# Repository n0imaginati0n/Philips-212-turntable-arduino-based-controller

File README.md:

# Philips-212-turntable-arduino-based-controller

A controller upgrade for the classic Philips 212 Hi-Fi turntable.
Replaces all touch switch, motor control, and auto-off functions with an Arduino Uno clone

Files include Arduino sketch and KiCad files

Fork of the

[lens42 project](https://github.com/lens42/Philips-212-turntable-arduino-based-controller)

[Details:](https://lensprojects.wordpress.com/2019/01/08/philips-212-turntable-controller-upgrade/)

# Improvements

* Use of the Ardino Pro Mini
* Self-made PCB. There are not so many parts there, it can be etched at home
* review schematics
    - add necessay loading on the LM780x. According to the datasheet, minimal current is 5..10 mA.
    - LM780x don't like to work on big capacitance load - they need protection diodes
    - small filtering caps on the sensors input to filter noise. input cirquit can be taken from original GA212 schematics
    - resistance in the MOSFET gate cirquit to limit the pulse current through MCU output
    - allow TH componets usage, reuse some items from original board
    - IP pins can be assigned better to make less croddings on the PCB
    - sensor button connections can be done better. but analog curcit rules should be taken into account
    - as I plan to etch teh single-layer board at home, I will use tow heatsinks for LM780x instead of the PCB polygons. There 
        is a lot of space under the PCB.
* Programming UART pins and reset button on the board. Pro Mini hasn't USB socket.
* Review the firmware
    - make it interactive
    - all initially predefined values can be set by UART
    - keep configuration values in the FLASH

# Arduino Power

Almost all Arduino boards has an LDO onboard. This LDO allows up to 16V input and can supply arduino and external cirquit 
with the +3.3V/+5V <150mA power according to the Arduino version. All the MCU ATMEGA328 allow both +3.3V and +5V power. The 
difference is that on lower voltage Arduino works stable with less crystal frequency. That is why +3.3V has 8MHz crystal and 
+5V has 16MHz crystal. Any version of the Arduino Pro Mini can safely be supplied with the +5V.

LM393 can operate with power in +2V..+36V range, means it can be perfectly powered from any version of the Arduino. It 
cosumes <20mA, this current is a maximal sink current and should be lower than that.

Unfortunately, my Arduino LDO is broken because of the previous experiments, that is why I kept the external LDO here and lead 
the +5V to the Arduino Vcc input. Vcc - is a direct way to teh Arduino power excluding on-baord LDO.

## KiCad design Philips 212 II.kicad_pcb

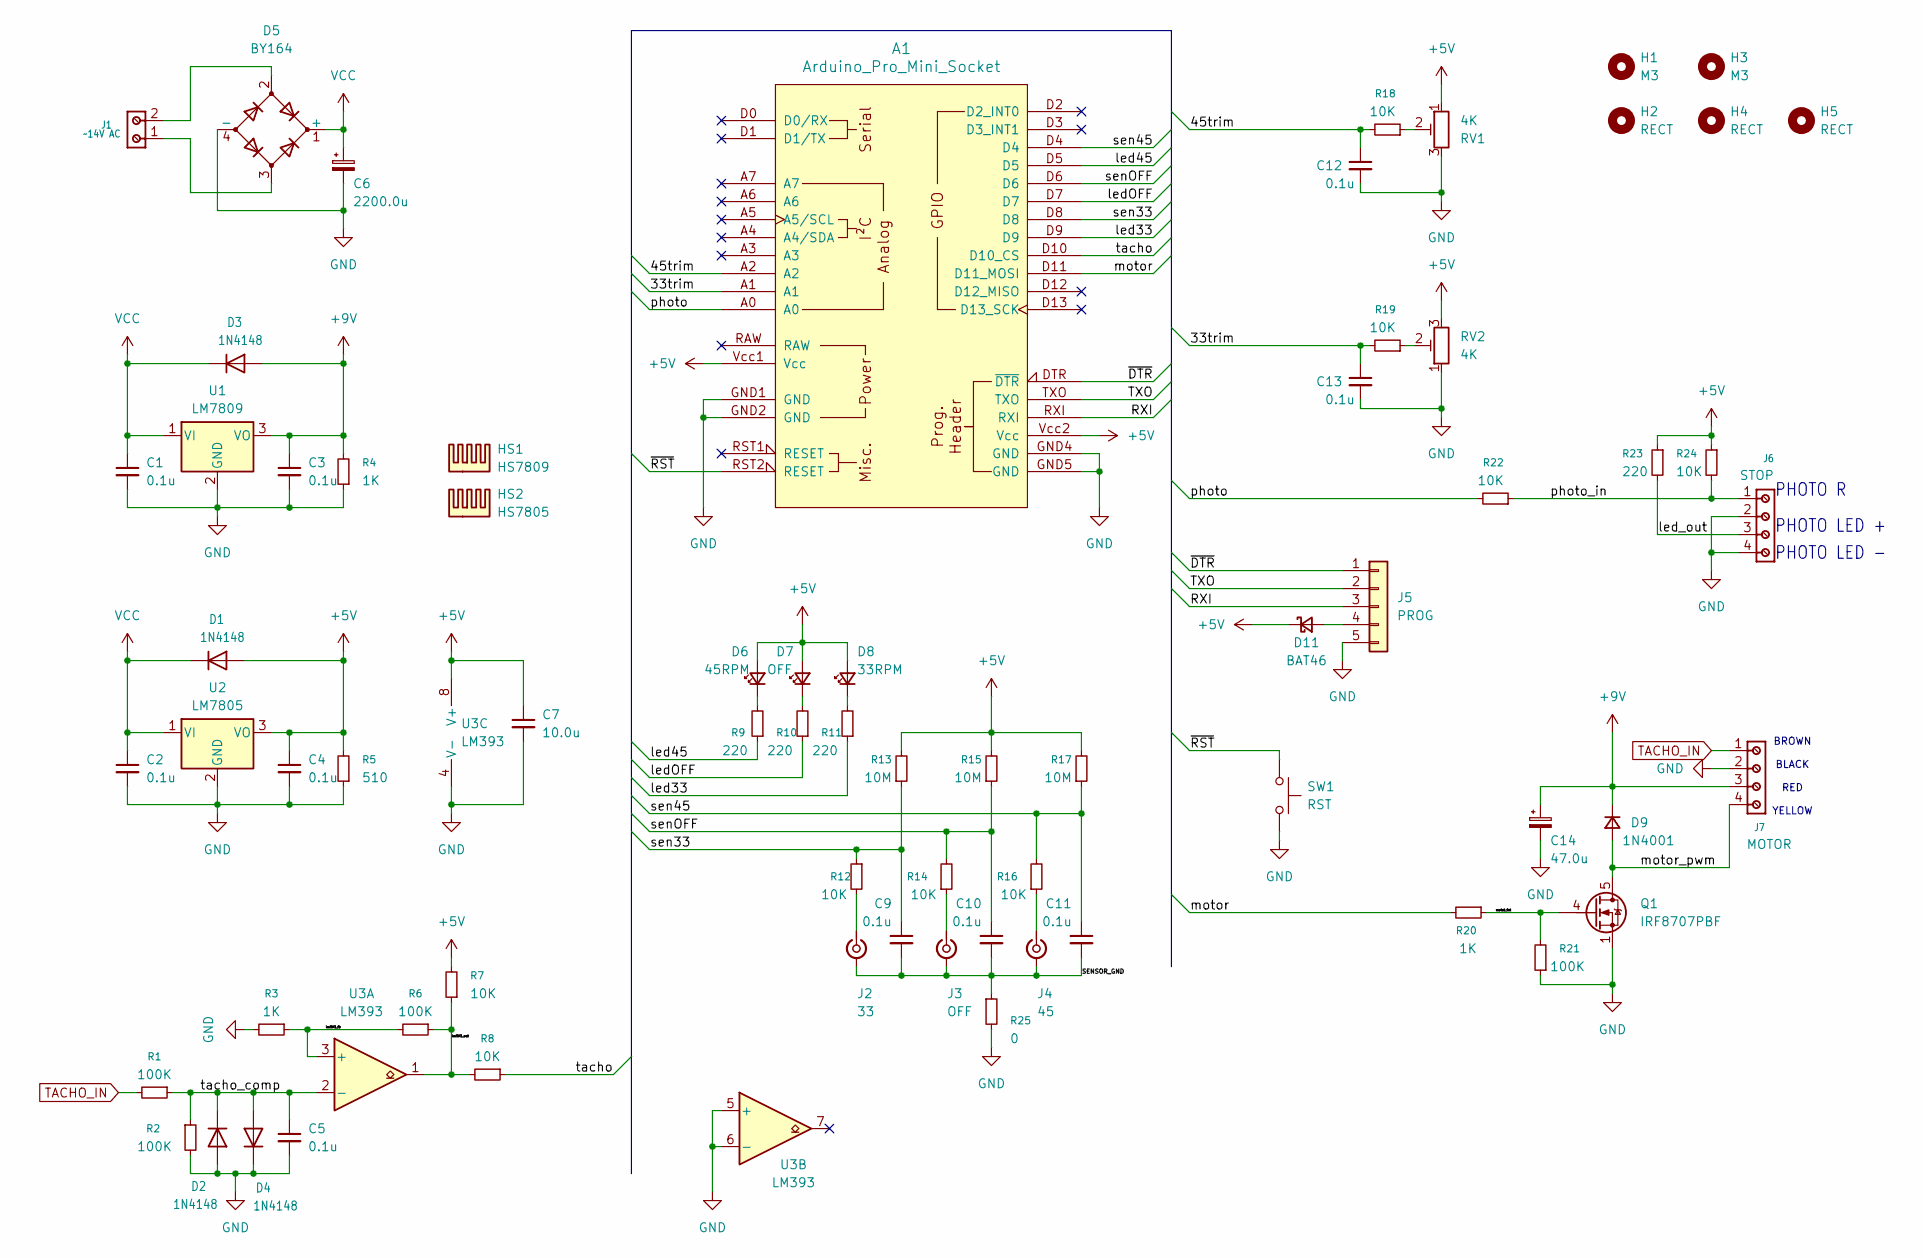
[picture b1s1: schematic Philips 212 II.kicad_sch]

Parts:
A1: Arduino_Pro_Mini_Socket
C1, C2, C3, C4, C5, C9, C10, C11, C12, C13: 0.1u; C_0805_2012Metric_Pad1.18x1.45mm_HandSolder
C6: 2200.0u; CP_Radial_D16.0mm_P7.50mm
C7: 10.0u; CP_Radial_D8.0mm_P3.50mm
C14: 47.0u; CP_Radial_D8.0mm_P3.50mm
D1, D3: 1N4148; D_MELF_Handsoldering
D2, D4: 1N4148; D_DO-35_SOD27_P7.62mm_Horizontal
D5: BY164; Diode_Bridge_19.0x3.5x10.0mm_P5.0mm
D6: 45RPM; LED_D5.0mm_Horizontal_O6.35mm_Z15.0mm
D7: OFF; LED_D5.0mm_Horizontal_O6.35mm_Z15.0mm
D8: 33RPM; LED_D5.0mm_Horizontal_O6.35mm_Z15.0mm
D9: 1N4001; D_DO-41_SOD81_P10.16mm_Horizontal
D11: BAT46; D_DO-35_SOD27_P7.62mm_Horizontal
H1, H3: M3; MountingHole_3.2mm_M3
H2, H4, H5: RECT; MountingHole_6mm
HS1: HS7809; FISHER-FK211-32_TO220_Horizontal
HS2: HS7805; FISHER-FK211-32_TO220_Horizontal
J1: ~14V AC; Altech_AK100_1x02_P5.00mm
J2: 33; Altech_AK100_1x02_P5.00mm
J3: OFF; Altech_AK100_1x02_P5.00mm
J4: 45; Altech_AK100_1x02_P5.00mm
J5: PROG; PinHeader_1x05_P2.54mm_Vertical
J6: STOP; Altech_AK100_1x04_P5.00mm
J7: MOTOR; Altech_AK100_1x04_P5.00mm
Q1: IRF8707PBF; PowerPAK_SO-8_Single
R1, R2, R21: 100K; R_0805_2012Metric_Pad1.20x1.40mm_HandSolder
R3: 1K; R_0805_2012Metric_Pad1.20x1.40mm_HandSolder
R4, R20: 1K; R_Axial_DIN0207_L6.3mm_D2.5mm_P7.62mm_Horizontal
R5: 510; R_Axial_DIN0207_L6.3mm_D2.5mm_P7.62mm_Horizontal
R6: 100K; R_Axial_DIN0207_L6.3mm_D2.5mm_P7.62mm_Horizontal
R7, R12, R14, R16, R18, R19, R22, R24: 10K; R_0805_2012Metric_Pad1.20x1.40mm_HandSolder
R8: 10K; R_Axial_DIN0207_L6.3mm_D2.5mm_P7.62mm_Horizontal
R9, R10, R11, R23: 220; R_Axial_DIN0207_L6.3mm_D2.5mm_P7.62mm_Horizontal
R13, R15, R17: 10M; R_Axial_DIN0411_L9.9mm_D3.6mm_P15.24mm_Horizontal
R25: 0; R_0805_2012Metric_Pad1.20x1.40mm_HandSolder
RV1, RV2: 4K; Potentiometer_ACP_CA14V-15_Vertical_Hole
SW1: RST; SW_PUSH_6mm
U1: LM7809; TO-220-3_Horizontal_TabDown
U2: LM7805; TO-220-3_Horizontal_TabDown
U3: LM393; SOIC-8_3.9x4.9mm_P1.27mm

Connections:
+5V: A1.Vcc1 (Vcc), A1.Vcc2 (Vcc), C4.1, C7.1, D1.2 (A), D6.2 (A), D7.2 (A), D8.2 (A), D11.1 (K), R5.2, R7.2, R13.2, R15.2, R17.2, R23.1, R24.1, RV1.1, RV2.3, U2.3 (VO), U3.8 (V+)
+9V: C3.1, C14.1, D3.2 (A), D9.1 (K), J7.3, R4.2, U1.3 (VO)
/33trim: A1.A1, C13.1, R19.2
/45trim: A1.A2, C12.1, R18.2
/RXI: A1.RXI, J5.3
/SENSOR_GND: C9.2, C10.2, C11.2, J2.2 (Ext), J3.2 (Ext), J4.2 (Ext), R25.1
/TXO: A1.TXO, J5.2
/led33: A1.D9, R11.1
/led45: A1.D5, R9.1
/ledOFF: A1.D7, R10.1
/led_out: J6.3, R23.2
/lm393_fb: R3.1, R6.2, U3.3 (+)
/lm393_out: R6.1, R7.1, R8.2, U3.1
/motor: A1.D11 (D11_MOSI), R20.2
/motor_pwm: D9.2 (A), J7.4, Q1.5 (D)
/motot_fet: Q1.4 (G), R20.1, R21.2
/photo: A1.A0, R22.2
/photo_in: J6.1, R22.1, R24.2
/sen33: A1.D8, C9.1, R12.1, R13.1
/sen45: A1.D4, C11.1, R16.2, R17.1
/senOFF: A1.D6, C10.1, R14.2, R15.1
/tacho: A1.D10 (D10_CS), R8.1
/tacho_comp: C5.1, D2.1 (K), D4.2 (A), R1.1, R2.1, U3.2 (-)
/~DTR: A1.DTR (~DTR), J5.1
/~RST: A1.RST2 (RESET), SW1.1
GND: A1.GND1 (GND), A1.GND2 (GND), A1.GND4 (GND), A1.GND5 (GND), C1.2, C2.2, C3.2, C4.2, C5.2, C6.2, C7.2, C12.2, C13.2, C14.2, D2.2 (A), D4.1 (K), D5.4 (-), J5.5, J6.2, J6.4, J7.2, Q1.1 (S), Q1.2 (S), Q1.3 (S), R2.2, R3.2, R4.1, R5.1, R21.1, R25.2, RV1.3, RV2.1, SW1.2, U1.2 (GND), U2.2 (GND), U3.4 (V-), U3.5 (+), U3.6 (-)
unnamed: D5.2, J1.2
unnamed: D5.3, J1.1
unnamed: D6.1 (K), R9.2
unnamed: D7.1 (K), R10.2
unnamed: D8.1 (K), R11.2
unnamed: D11.2 (A), J5.4
unnamed: J2.1 (In), R12.2
unnamed: J3.1 (In), R14.1
unnamed: J4.1 (In), R16.1
unnamed: R18.1, RV1.2
unnamed: R19.1, RV2.2
TACHO_IN: J7.1, R1.2
VCC: C1.1, C2.1, C6.1, D1.1 (K), D3.1 (K), D5.1 (+), U1.1 (VI), U2.1 (VI)

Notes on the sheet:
PHOTO R
PHOTO LED -
BROWN BLACK RED YELLOW
PHOTO LED +

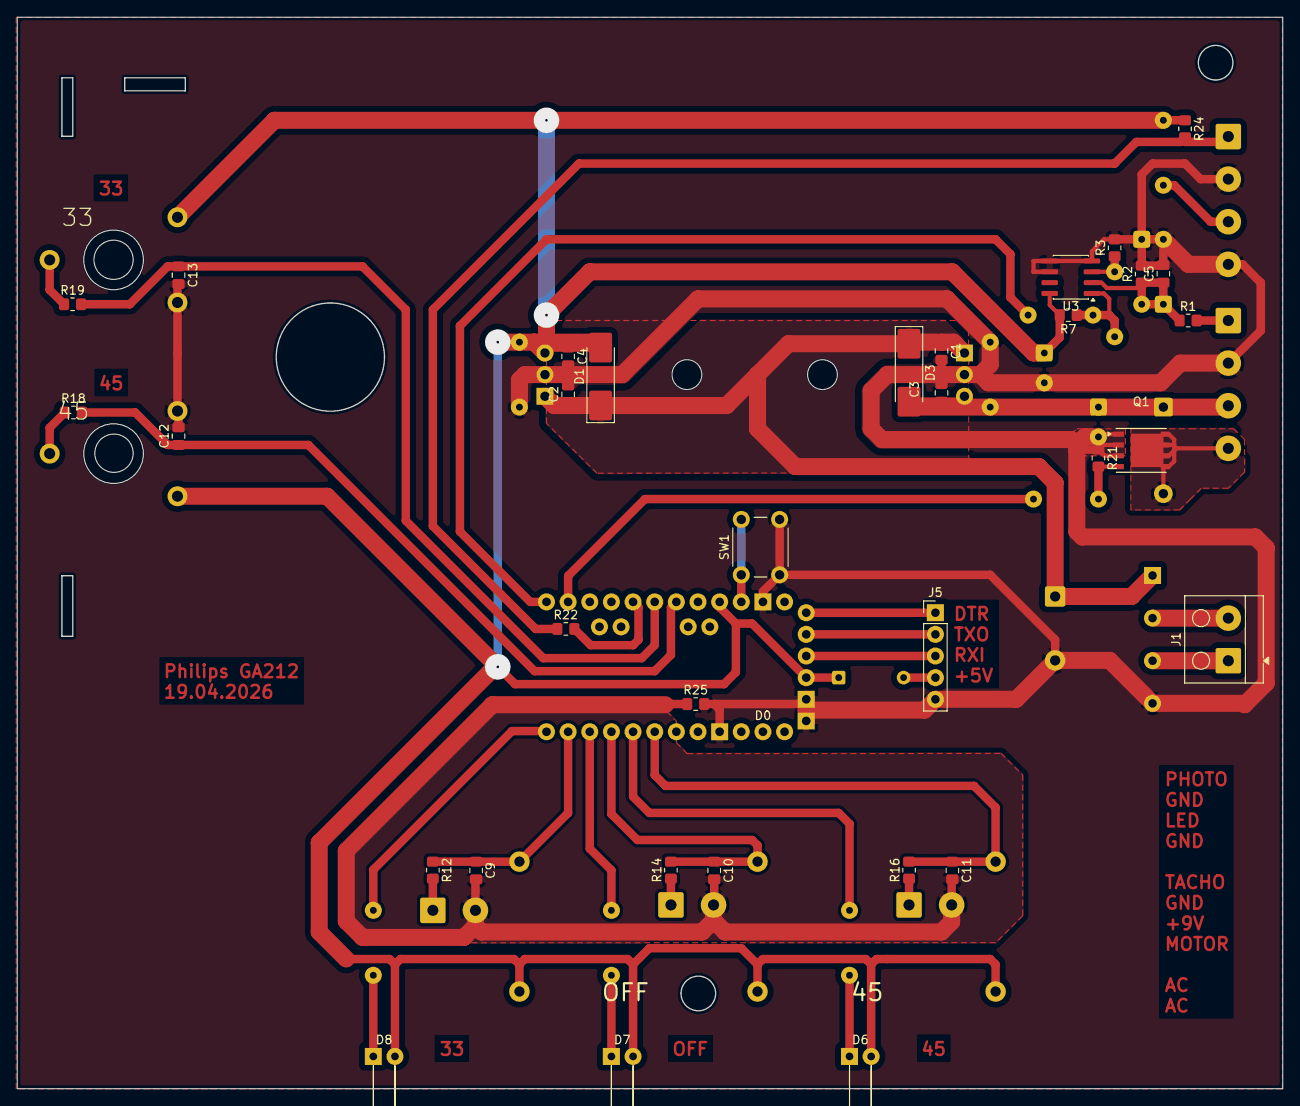
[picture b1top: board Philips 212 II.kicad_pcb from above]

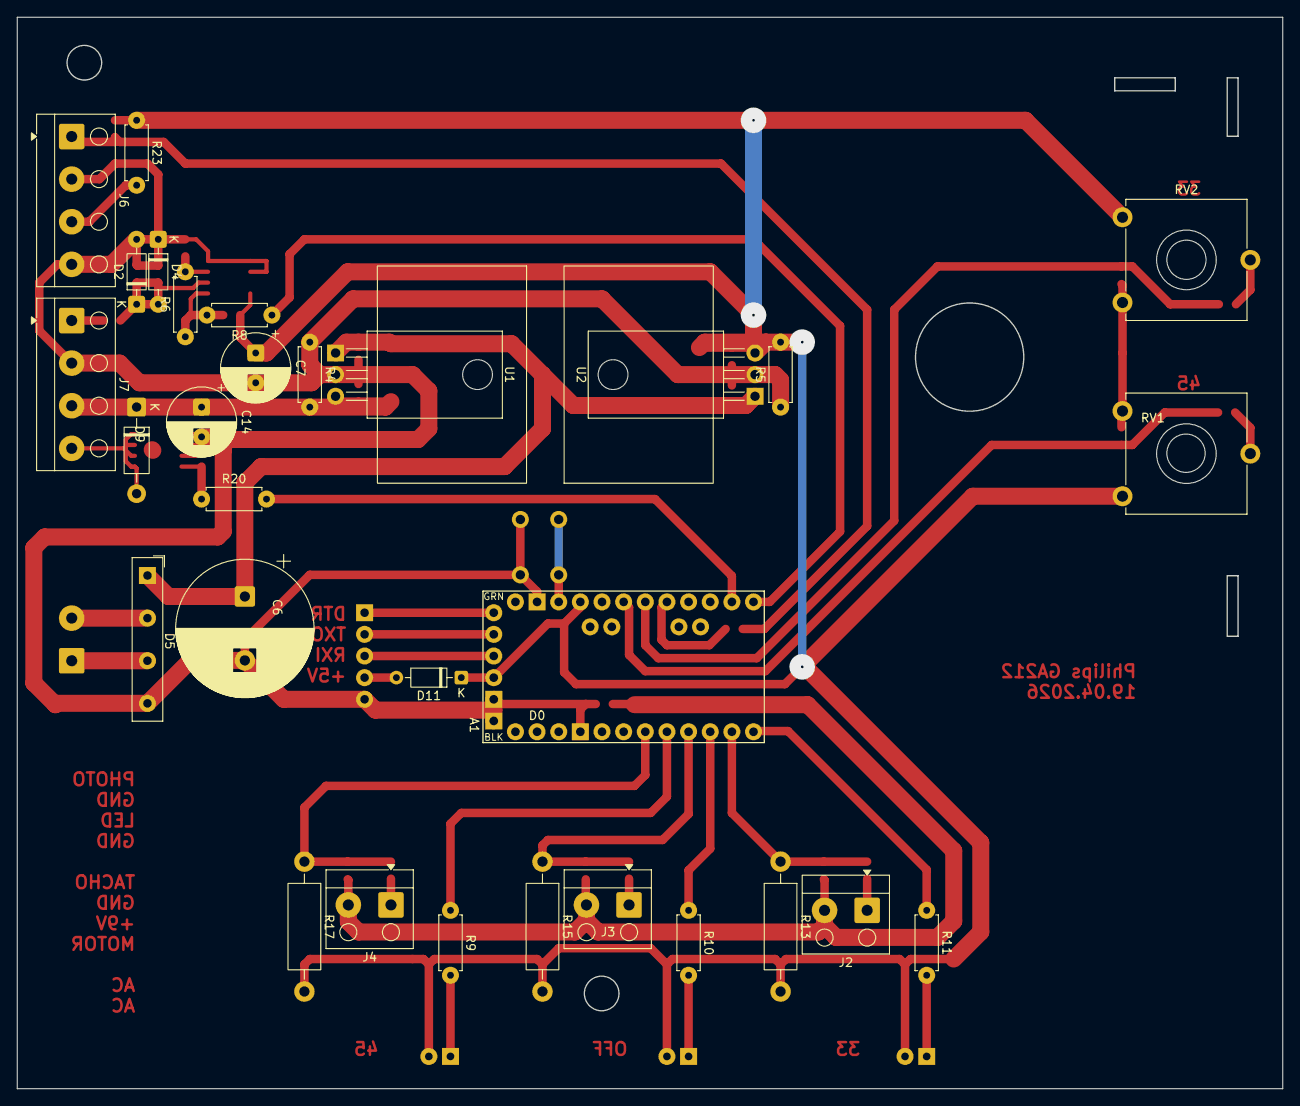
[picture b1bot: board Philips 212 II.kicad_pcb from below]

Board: 2 copper layers, 148.4 x 125.6 mm, 65 parts (32 on the bottom side), 39 nets.

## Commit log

2026-04-09 modify README.md
2026-04-21 version II of the schematics and board
2026-05-05 split the tasks
2026-05-16 attempt to make analytical PID paramns
2026-05-16 first functional version
